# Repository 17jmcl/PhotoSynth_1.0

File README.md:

# PhotoSynth
 PhotoSynth: A synth using Biodata to modulate effects. 
 
Date Updated Last: 05/02/22

Julie McLaughlin 
Thesis Project for Temple University 
Advisor: Dr. Adam Vidiksis 

Description (What it does, technology used, challenges and future features)
A synth with a 12 note keyboard using Biodata to modulate effects. 

It uses Teensy 3.5, a custom PCB board made with Fusion 360 Autodesk, and Teensyduino IDE. 

How to use the project:
Download SCH,PCB,Gerber, and BOM and open with your preferred developement software (example: Autodesk Fusion 360). Open ino files with Teensyduino or Arduino IDE, adjust your settings, and compile/run the code. 

-------------------------------------------------------------------------------

Dependencies: 
TeensyDuino: PJRC derivative of Arduino 
PJRC Audio Tool: Audio Library (PJRC)
Bounce2: Debouncing library for Arduino 

Credits:
Based on BiodataSonificationBreadboardKit from Sam Cusumano electricityforprogress and Instruo Scion 
Thanks to the help of my family, friends, and collaborators. 

------------------------------------------------------------------------------

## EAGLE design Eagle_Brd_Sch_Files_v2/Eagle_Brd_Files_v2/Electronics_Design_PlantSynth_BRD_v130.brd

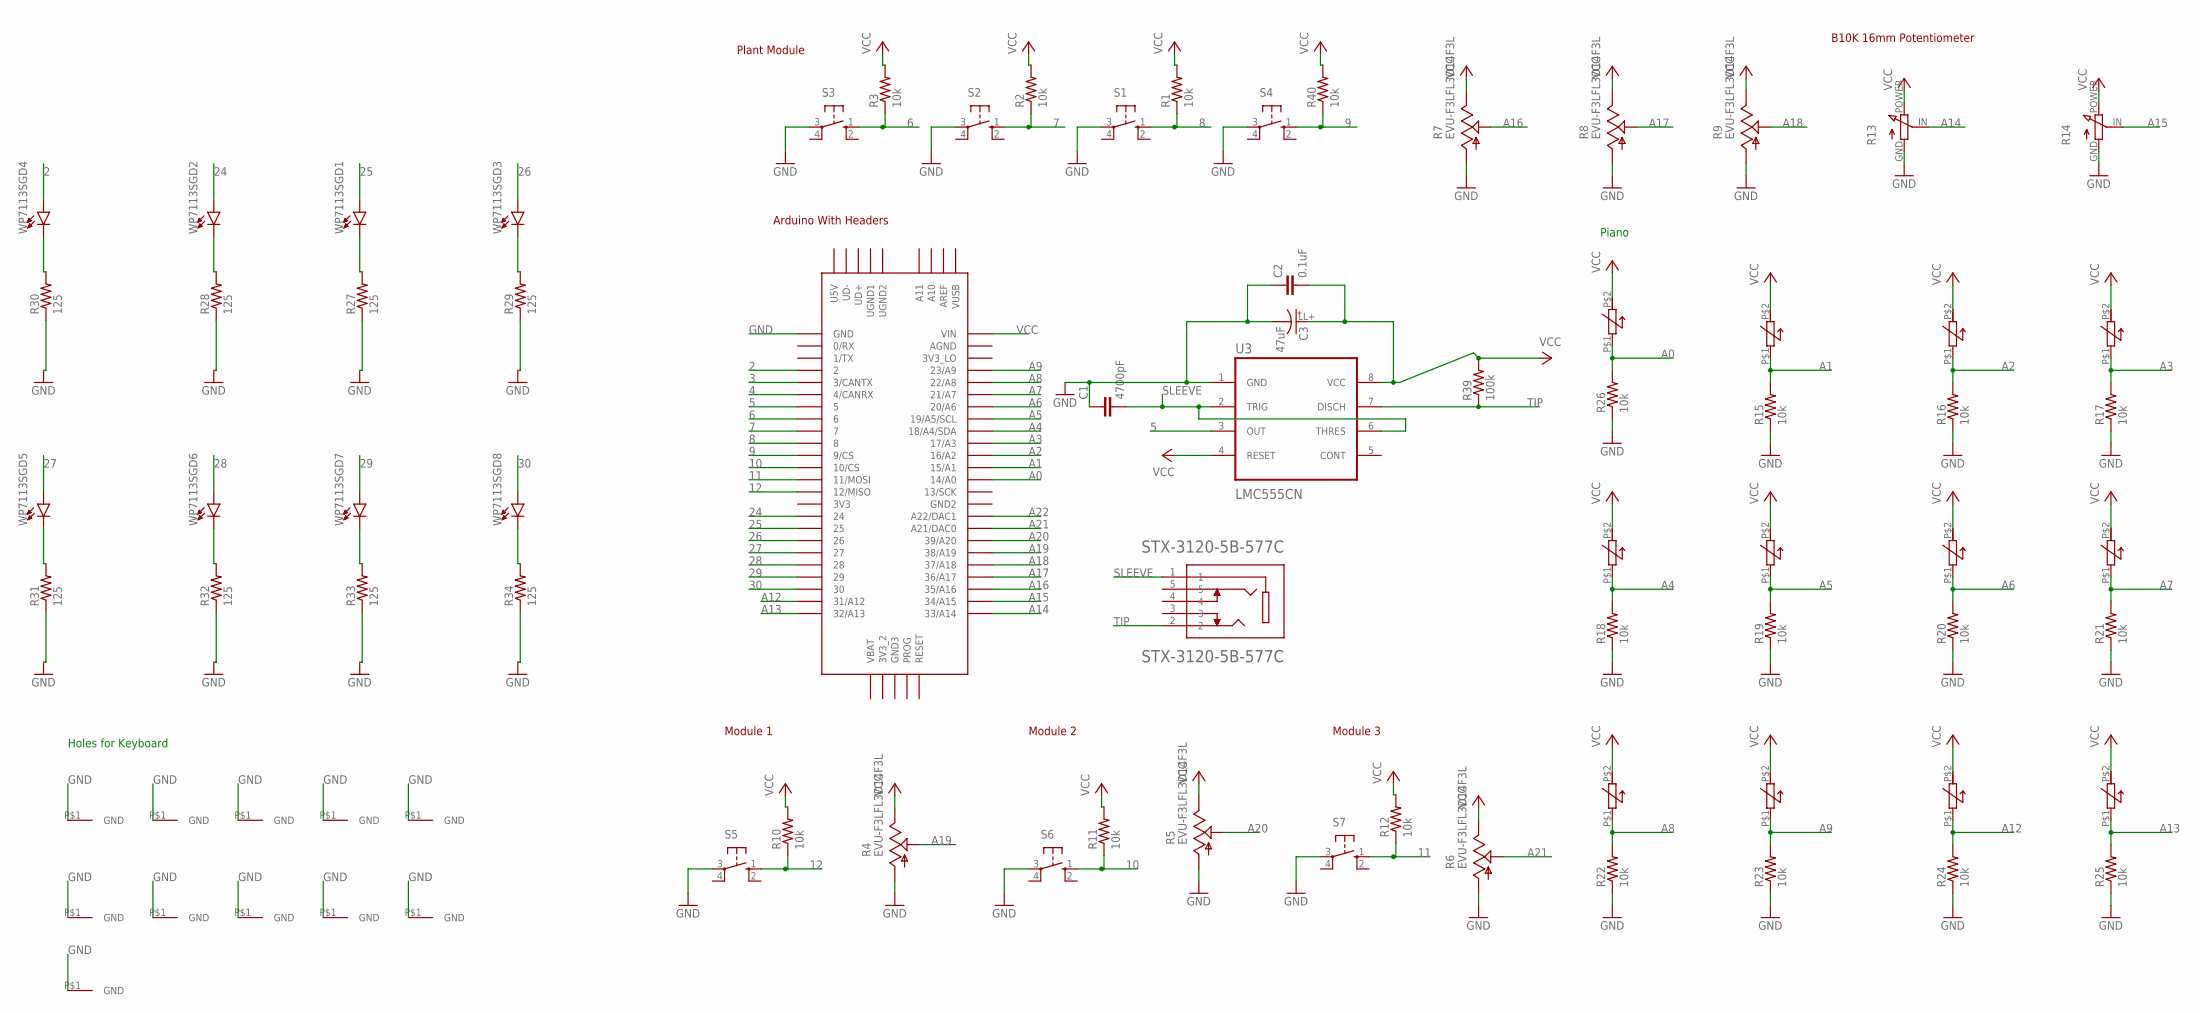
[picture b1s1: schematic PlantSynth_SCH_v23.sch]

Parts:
C1: 4700pF; C2.5-2
C2: 0.1uF; C2.5-2
C3: 47uF; ESK476M050AE3EA_47UF_CAP
FSR1, FSR2, FSR3, FSR4, FSR5, FSR6, FSR7, FSR8, FSR9, FSR10, FSR11, FSR12: FSR400_0.85; FSR400_.85
GND, GND37, GND38: MOUNTINGHOLE; MOUNTEDHOLE
R1, R2, R3, R10, R11, R12, R15, R16, R17, R18, R19, R20, R21, R22, R23, R24, R25, R26, R40: 10k; 0204/5
R4, R5, R6, R7, R8, R9: EVU-F3LFL3D14F3L; EVUFXL
R13, R14: B3B-XH-AB3B; B3B-XH-A
R27, R28, R29, R30, R31, R32, R33, R34: 125; 0204/5
R39: 100k; 0204/5
S1, S2, S3, S4, S5, S6, S7: B3F-1020; B3F-10XX
STX-3120-5B-577C: STX-3120-5B-577C
U3: LMC555CN; LMC555CN/NOPB-ND
U$1: TEENSY_3.5/3.6
U$2, U$3, U$4, U$5, U$6, U$7, U$8, U$9: MOUNTINGHOLE; MOUNTEDHOLE
WP7113SGD1, WP7113SGD2, WP7113SGD3, WP7113SGD4, WP7113SGD5, WP7113SGD6, WP7113SGD7, WP7113SGD8: LEDGREEN_KINGBRIGHT_WP7113SGD; LEDGREENDIFFUSED5MM

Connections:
2: U$1.2, WP7113SGD4.A+ (ANODE(+))
3: U$1.3/CANTX
4: U$1.4/CANRX
5: U3.3 (OUT), U$1.5
6: R3.1, S3.1 (S), U$1.6
7: R2.1, S2.1 (S), U$1.7
8: R1.1, S1.1 (S), U$1.8
9: R40.1, S4.1 (S), U$1.9/CS
10: R11.1, S6.1 (S), U$1.10/CS
11: R12.1, S7.1 (S), U$1.11/MOSI
12: R10.1, S5.1 (S), U$1.12/MISO
24: U$1.24, WP7113SGD2.A+ (ANODE(+))
25: U$1.25, WP7113SGD1.A+ (ANODE(+))
26: U$1.26, WP7113SGD3.A+ (ANODE(+))
27: U$1.27, WP7113SGD5.A+ (ANODE(+))
28: U$1.28, WP7113SGD6.A+ (ANODE(+))
29: U$1.29, WP7113SGD7.A+ (ANODE(+))
30: U$1.30, WP7113SGD8.A+ (ANODE(+))
A0: FSR12.P$1 (OUT/GND), R26.2, U$1.14/A0
A1: FSR1.P$1 (OUT/GND), R15.2, U$1.15/A1
A2: FSR2.P$1 (OUT/GND), R16.2, U$1.16/A2
A3: FSR3.P$1 (OUT/GND), R17.2, U$1.17/A3
A4: FSR4.P$1 (OUT/GND), R18.2, U$1.18/A4/SDA
A5: FSR5.P$1 (OUT/GND), R19.2, U$1.19/A5/SCL
A6: FSR6.P$1 (OUT/GND), R20.2, U$1.20/A6
A7: FSR7.P$1 (OUT/GND), R21.2, U$1.21/A7
A8: FSR8.P$1 (OUT/GND), R22.2, U$1.22/A8
A9: FSR9.P$1 (OUT/GND), R23.2, U$1.23/A9
A12: FSR10.P$1 (OUT/GND), R24.2, U$1.31/A12
A13: FSR11.P$1 (OUT/GND), R25.2, U$1.32/A13
A14: R13.IN, U$1.33/A14
A15: R14.IN, U$1.34/A15
A16: R7.IN, U$1.35/A16
A17: R8.IN, U$1.36/A17
A18: R9.IN, U$1.37/A18
A19: R4.IN, U$1.38/A19
A20: R5.IN, U$1.39/A20
A21: R6.IN, U$1.21/DAC0 (A21/DAC0)
A22: U$1.A22/DAC1
GND: C1.1, C2.1, C3.LL- (-), GND.P$1, GND37.P$1, GND38.P$1, R4.GND, R5.GND, R6.GND, R7.GND, R8.GND, R9.GND, R13.GND, R14.GND, R15.1, R16.1, R17.1, R18.1, R19.1, R20.1, R21.1, R22.1, R23.1, R24.1, R25.1, R26.1, R27.1, R28.1, R29.1, R30.1, R31.1, R32.1, R33.1, R34.1, S1.3, S2.3, S3.3, S4.3, S5.3, S6.3, S7.3, U3.1 (GND), U$1.GND, U$2.P$1, U$3.P$1, U$4.P$1, U$5.P$1, U$6.P$1, U$7.P$1, U$8.P$1, U$9.P$1
unnamed: R28.2, WP7113SGD2.C- (CATHODE(-))
unnamed: R27.2, WP7113SGD1.C- (CATHODE(-))
unnamed: R29.2, WP7113SGD3.C- (CATHODE(-))
unnamed: R30.2, WP7113SGD4.C- (CATHODE(-))
unnamed: R31.2, WP7113SGD5.C- (CATHODE(-))
unnamed: R32.2, WP7113SGD6.C- (CATHODE(-))
unnamed: R33.2, WP7113SGD7.C- (CATHODE(-))
unnamed: R34.2, WP7113SGD8.C- (CATHODE(-))
SLEEVE: C1.2, STX-3120-5B-577C.1, U3.2 (TRIG), U3.6 (THRES)
TIP: R39.1, STX-3120-5B-577C.2, U3.7 (DISCH)
VCC: C2.2, C3.LL+ (+), FSR1.P$2 (VCC), FSR2.P$2 (VCC), FSR3.P$2 (VCC), FSR4.P$2 (VCC), FSR5.P$2 (VCC), FSR6.P$2 (VCC), FSR7.P$2 (VCC), FSR8.P$2 (VCC), FSR9.P$2 (VCC), FSR10.P$2 (VCC), FSR11.P$2 (VCC), FSR12.P$2 (VCC), R1.2, R2.2, R3.2, R4.PWR (POWER), R5.PWR (POWER), R6.PWR (POWER), R7.PWR (POWER), R8.PWR (POWER), R9.PWR (POWER), R10.2, R11.2, R12.2, R13.POWER, R14.POWER, R39.2, R40.2, U3.4 (RESET), U3.8 (VCC), U$1.VIN

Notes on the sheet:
B10K 16mm Potentiometer
Plant Module
Module 1
Module 2
Module 3
Arduino With Headers
Piano
Holes for Keyboard

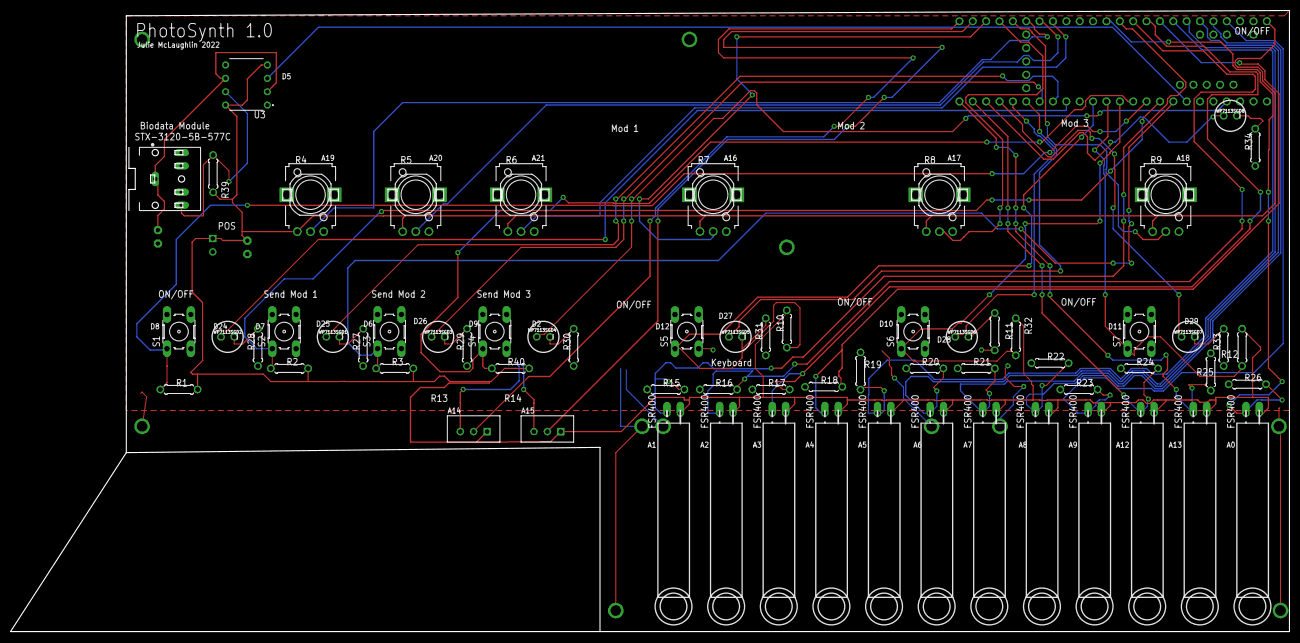
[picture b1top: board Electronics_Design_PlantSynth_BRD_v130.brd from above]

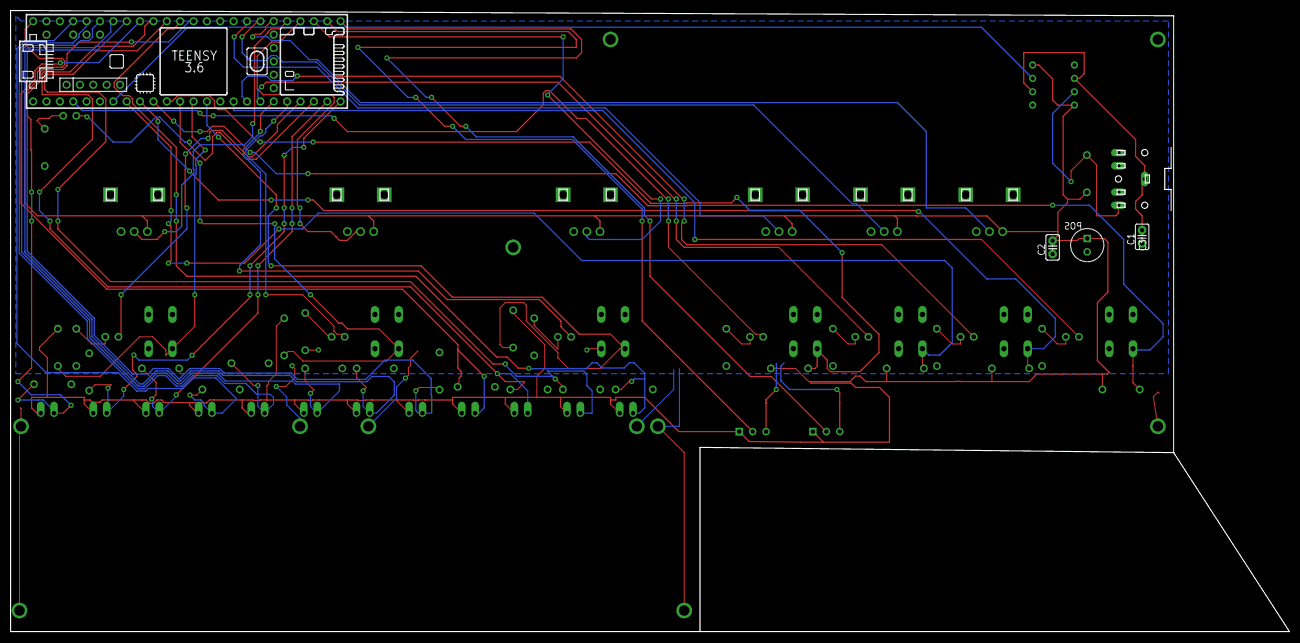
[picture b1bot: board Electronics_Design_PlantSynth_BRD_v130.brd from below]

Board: 2 copper layers, 242.8 x 117.9 mm, 80 parts (4 on the bottom side), 48 nets.

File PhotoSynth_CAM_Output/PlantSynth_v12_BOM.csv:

"Qty";"Value";"Device";"Package";"Parts";"Description";"MANUFACTURER";"MF";"MPN";"OC_FARNELL";"OC_NEWARK";"PARTREV";"POPULARITY";"SPICEPREFIX";"STANDARD";
"2";"";"B3B-XH-AB3B";"B3B-XH-A";"R13, R14";"16mm pot from DHV B10K with B3B-XH-A 3 pin header";"";"";"";"";"";"";"";"";"";
"7";"";"B3F-1020";"B3F-10XX";"S1, S2, S3, S4, S5, S6, S7";"OMRON SWITCH";"";"";"B3F-1000";"176432";"36M3542";"";"72";"";"";
"8";"";"LEDGREEN_KINGBRIGHT_WP7113SGDWP7113SGD";"LEDGREENDIFFUSED5MM";"WP7113SGD1, WP7113SGD2, WP7113SGD3, WP7113SGD4, WP7113SGD5, WP7113SGD6, WP7113SGD7, WP7113SGD8";"WP7113SGD";"";"";"";"";"";"";"";"";"";
"1";"0.1uF";"C2.5/2";"C2.5-2";"C2";"CAPACITOR";"";"";"";"";"";"";"28";"";"";
"1";"100k";"R-US_R0603";"R0603";"R39";"RESISTOR, American symbol";"";"";"";"";"";"";"77";"R";"";
"19";"10k";"R-US_R0603";"R0603";"R1, R2, R3, R10, R11, R12, R15, R16, R17, R18, R19, R20, R21, R22, R23, R24, R25, R26, R40";"RESISTOR, American symbol";"";"";"";"";"";"";"77";"R";"";
"8";"125";"R-US_R0603";"R0603";"R27, R28, R29, R30, R31, R32, R33, R34";"RESISTOR, American symbol";"";"";"";"";"";"";"77";"R";"";
"1";"4700pF";"C2.5/2";"C2.5-2";"C1";"CAPACITOR";"";"";"";"";"";"";"28";"";"";
"1";"47uF";"ESK476M050AE3EAESK476M050AE3EA";"ESK476M050AE3EA_47UF_CAP";"C3";"Capacitor Polarised - ANSI";"";"";"";"";"";"";"";"";"";
"6";"EVU-F3LFL3D14F3L";"EVU-F3LFL3D14F3L";"EVUFXL";"R4, R5, R6, R7, R8, R9";"9 mm Square Rotary Potentiometers";"";"";"";"";"";"";"0";"";"";
"12";"FSR400_0.85";"FSR400_0.85";"FSR400_.85";"FSR1, FSR2, FSR3, FSR4, FSR5, FSR6, FSR7, FSR8, FSR9, FSR10, FSR11, FSR12";"FSR400";"";"";"";"";"";"";"";"";"";
"1";"LMC555CN";"LMC555CN";"LMC555CN/NOPB-ND";"U3";"LMC555CN/NOPB-ND PDIP(8) TI 9.81x6.35mm";"";"";"";"";"";"";"";"";"";
"1";"SJ1-3525NG";"SJ1-3525NG";"CUI_SJ1-3525NG";"CONNJACKSTEREO_3.5MM_R/A";"3.5 mm Right-Angle Stereo Jack, 5 Pin PCB Mount, Isolated Ground";"CUI";"";"";"";"";"1.01";"";"";"Manufacturer recommendation";
"1";"TEENSY_3.5/3.6";"TEENSY_3.5/3.6";"TEENSY_3.5/3.6";"U$1";"";"";"";"";"";"";"";"";"";"";

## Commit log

2022-04-05 Updated Readme
    Updated Readme
2022-04-05 Autodesk and INO_ref Add
    Added Autodesk files and INO reference code
2022-04-05 PCBImageAdd
    Added PCB Image
2022-04-06 Added AstableMultivibrator code
    Astable Multivibrator with 100ohm resistors and the 47uF polarized capacitor V5 producing around 80 Hertz (Basis for Plant reading)
2022-04-06 Updated files
    Updated files
2022-04-07 Updated Files
    Update with PCB
2022-04-23 New Files added: Building out whole program
    New Files added: Building out whole program
2022-04-23 Added Plant and Keys Mods
    Added Plant and Keys Mods
2022-04-26 This one works
2022-05-02 Final commit

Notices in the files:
parts and their libraries:
KingBright_LED_WP7113SGD: Licensing: Creative Commons ShareAlike 4.0 International - https://creativecommons.org/licenses/by-sa/4.0
